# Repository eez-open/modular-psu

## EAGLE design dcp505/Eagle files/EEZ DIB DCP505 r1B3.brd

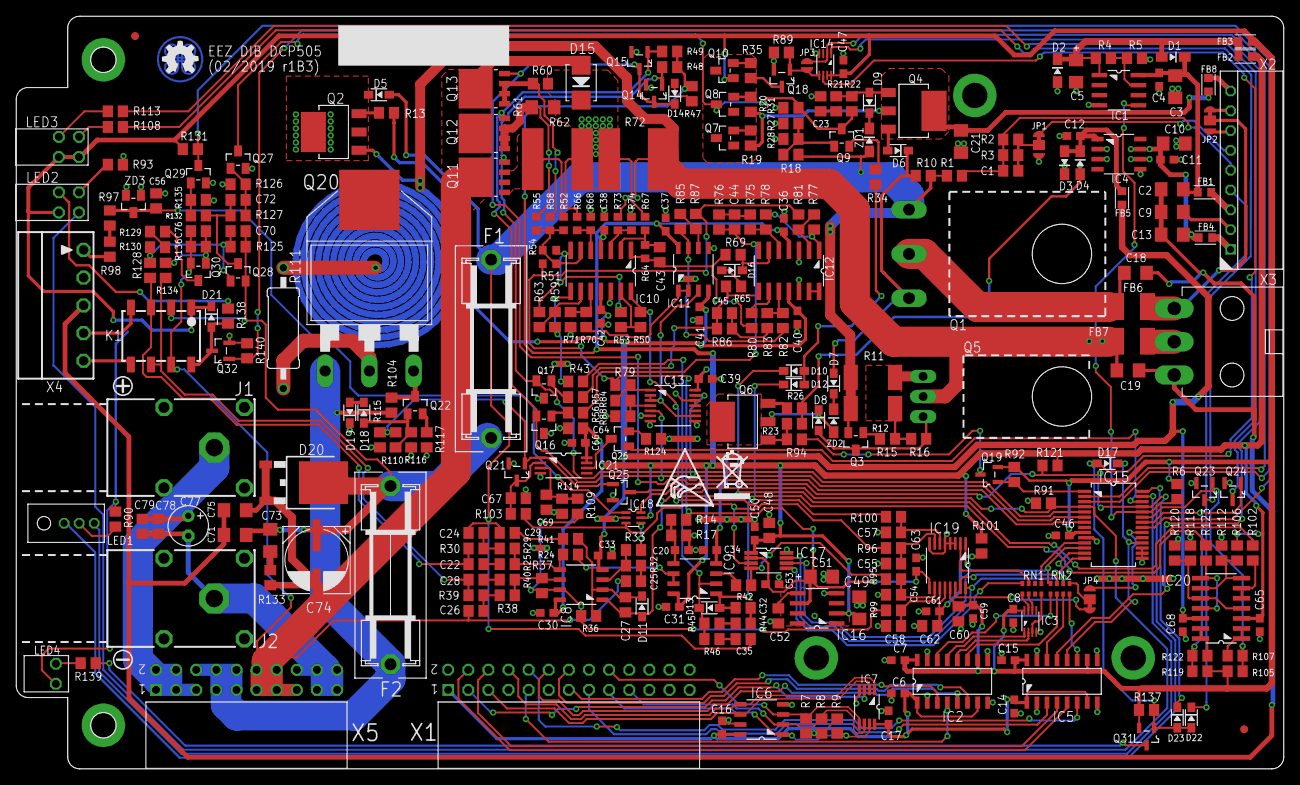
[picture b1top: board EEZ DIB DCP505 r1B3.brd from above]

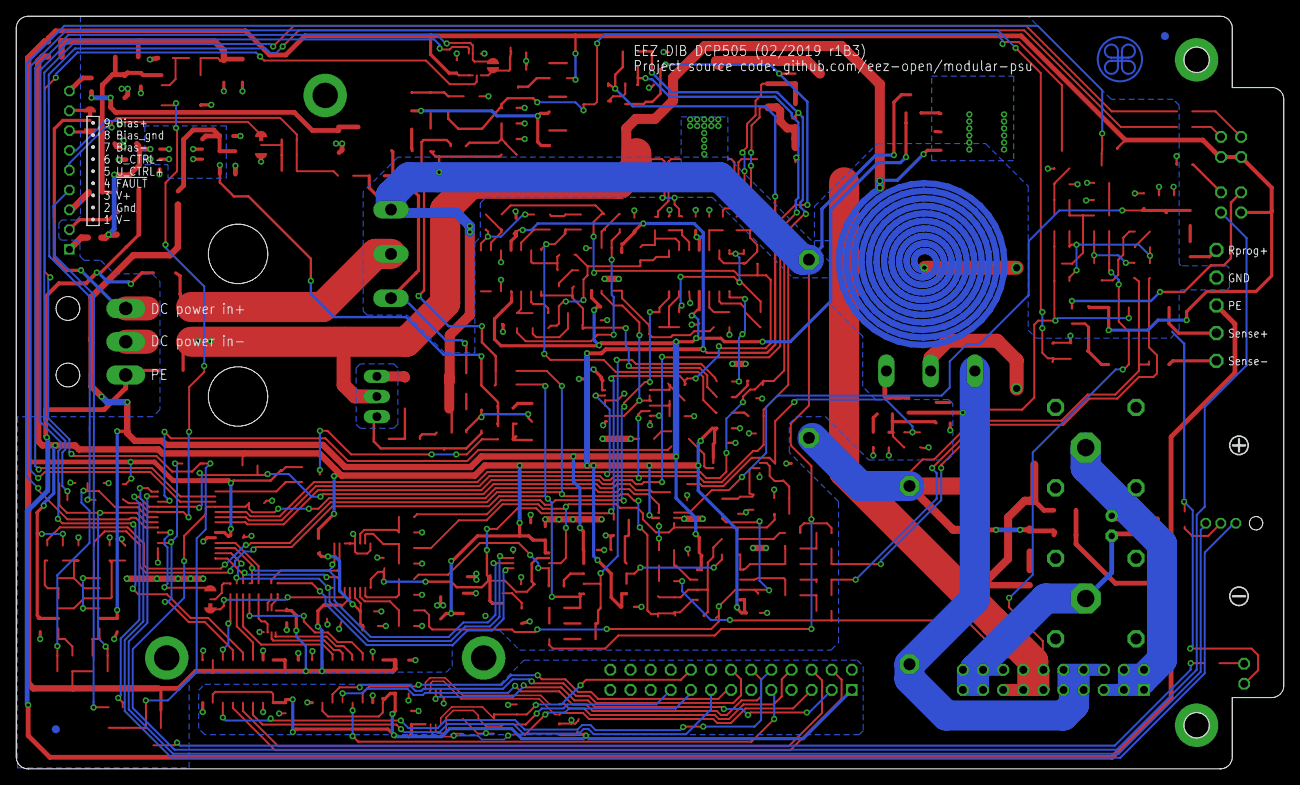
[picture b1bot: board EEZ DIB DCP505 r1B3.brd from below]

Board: 2 copper layers, 160.0 x 95.0 mm, 335 parts (4 on the bottom side), 221 nets.

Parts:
C1, C43: 47n; C0805
C2, C9, C13, C18, C19: 47n; C1206
C3, C10, C49: 10u; C1206
C4, C6, C7, C8, C11, C12, C14, C15, C16, C17, C20, C30, C31, C33, C34, C36, C37, C38, C39, C40, C41, C42, C46, C47, C50, C53, C59, C61, C63, C65, C66, C68: 100n; C0603
C5, C51: 4u7; EC1206
C21: 1u/100V; C1206
C22, C28: 47p; C0805
C23, C44, C45, C56, C70, C76: 10n; C0805
C24, C25, C26, C29, C72: 2n2; C0805
C27: 220p; C0805
C32, C35, C67, C69: 1n; C0805
C48, C52, C60, C62, C64: 1u; C0805
C54, C55, C57, C58: 3n3; C0805
C71, C75: 10n/200V; C1206
C73: 470n; C1206
C74: HHXC630ARA330MHA0G; CAPAE830X1050N
C77: N.C.; ECAP2/5
C78, C79: N.C.; C0805
D1, D2, D3, D4: 1N5819HW-7-F; SOD323-W
D5, D6, D7, D8, D9, D10, D11, D12, D13, D14, D16, D17, D18, D19, D21, D22, D23: BAS316; SOD323-R
D15: SK55; SMB
D20: SK10100D1-DIO; TO252-L
EEZ_SIGNATURE: SIGNATURESMALL; SIGNATURE_5MM
F1, F2: ZH32
FB1, FB2, FB3, FB4, FB5, FB8: BLM18AG102SH1D; BEAD0603
FB6, FB7: BLM41PG600SN1L; L1812
FM1, FM2: FIDUCIAL_2; FIDUCIAL_DUAL
IC1: LP2951; SOIC127P600X175-8N
IC2, IC5: SI8641BB-B-IS1; SOIC-16
IC3: SN74LVC1G139DCUR; DCU8
IC4: MC79L05; SOIC127P600X173-8N
IC6: AT24C04D-SSHM-T; SOIC127P600X173-8N
IC7: TMP1075AIDGK; DGK8
IC8, IC11: MC33272ADR2G; SOIC127P600X173-8N
IC9: MC33274ADR2G; SOIC127P600X173-8N
IC10: OPA4197IDR; SOIC127P600X175-14N
IC12: MC33274ADR2G; SOIC127P600X175-14N
IC13: 74HC4066PW; SOP65P640X120-14N
IC14: 74AUP1G74DC.125; DCU8
IC15: MCP23S17-E/SS; SOP65P780X200-28N
IC16: REF5025AIDR; SOIC127P600X175-8N
IC17: DAC8552IDGKR; DGK8-M
IC18: SN74LVC1G3157DCKR; SOT65P210X110-6N
IC19: ADS1120IPWR; PW(R-PDSO-G16)
IC20: LM339D; SOIC127P600X175-14N
IC21: LM211PWR; PW8_TSSOP8
J1: FCR7350R; S16N-PC
J2: FCR7350B; S16N-PC
JP1, JP2, JP4: JP3-CUT
JP3: JP2-CUT
K1: G6K-2F-5DC; G6K-2F
KK1, KK2: PCB-MB
LED1: L-42WUM/1EGWT; L-42WUM-1EGWT
LED2: L-934EB/2ID; L-934EB
LED3: L-934EB/1Y1ID-RV; L-934EB
LED4: OSY5LU3E34X-3F1A; OSG8
Q1: IRFP250MPBF; TO247BH-CLR2
Q2, Q4, Q6: BCP56-16.115; SOT230P700X180-4N
Q3: BC856C; SOT23-BEC
Q5: STF10P6F6; TO220H-CLR2
Q7, Q8, Q16, Q17, Q28: MMBT5401; SOT23-BEC
Q9, Q10, Q26, Q27, Q29, Q30: MMBT5551; SOT23-BEC
Q11, Q12, Q13: PSMN0R9-25YLC; SOT669
Q14, Q15, Q18, Q21, Q23, Q24, Q25, Q32: 2N7002; SOT103P240X110-3N
Q19, Q31: BSS84P; SOT95P237X112-3N
Q20: BTA26-600; TOP3_TRIAC_NOHOLE
Q22: FMMT493TA; SOT23-BEC
R1, R89, R92, R116, R140: 100K; R0805
R2, R107, R122: 5K6; R0805
R3: 82K; R0805
R4, R18: 16K; R0805
R5, R105, R119: 5K1; R0805
R6, R7, R8, R9, R14, R25, R33, R36, R40, R43, R45, R46, R53, R59, R63, R69, R70, R71, R75, R80, R81, R83, R85, R87, R94, R102, R103, R114, R115, R118, R120, R123, R131, R132, R137: 10K; R0805
R10, R23, R44, R47, R48, R49, R65, R77, R79, R84, R88, R110, R124, R129: 1K; R0805
R11, R12: 3R9/2W; R2512
R13, R28, R109, R128, R134: 750R; R0805
R15, R16, R27, R42, R56, R57, R112, R130: 2K2; R0805
R17, R19, R20, R26, R32, R41, R95, R96, R99, R100: 220R; R0805
R21, R34, R93, R97, R98, R104, R138, R139: 470R; R0805
R22, R78, R82: 100R; R0805
R24, R37: 7K5 0.1%; R0805
R29, R38: 130K 0.1%; R0805
R30, R39: 24K 0.1%; R0805
R31: 51K; R0805
R35: 1K8; R0805
R50: 30K; R0805
R51: 7M5; R0603
R52, R55, R58: 3K 0.1%; R0603
R54, R68: 40K2 0.1%; R0603
R60, R133: 1R; R0805
R61: 0R1; R1206
R62, R72: 0R010; R_H2728
R64, R74: 499K 0.1%; R0603
R66, R67, R73: 1K 0.1%; R0603
R76, R86: 1M; R0805
R90: 270R; R0805
R91, R106, R126, R127, R135: 47K; R0805
R101: 10R; R0805
R108, R113, R125, R136: 330R; R0805
R111: AC01000001007JA100; 0411/15
R117: 6R2; R0805
R121: 4K7; R0805
RN1, RN2: DR1206-33R-4/8; CAY16
SH1, SH2: SHORT_NOHOLE
U$1: RECYCLE_BIN1/8
U$6: ESD_SYMBOL
X1: ZL263-26DG; SSW-113-02-T-D-RA
X2: 22-05-7085; SPOX_22-05-7095
X3: 39-30-3035; MINIFIT_6659-3
X4: 1844249; MC1,5/5-G-3,5
X5: ZL263-20DG; SSW-110-02-T-D-RA
ZD1: BZX384-C15; SOD323-W
ZD2: PDZ6.2B; SOD323-W
ZD3: SLVU2.8-TP; SOT23

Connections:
!DP_DRIVE: Q6.1, R23.1, R94.1
!DRDY: IC19.14, JP4.NC
!FAULT: D22.C, X2.4
!FAULT_OUT: D17.A, D22.A, D23.A, IC14.6, Q31.1, R137.2
!OVP_EN: IC15.26, Q26.B
!OVP_FAULT: D23.C, IC15.25, Q25.3, R121.2
!RESET: D17.C, IC5.12, IC15.18
!SET_DP: IC15.1, Q19.1, R92.2
+3V3: C6.1, C14.1, C16.2, C17.1, IC2.1, IC2.7, IC5.1, IC5.7, IC6.8, IC7.8, R7.1, R8.1, R9.1, X1.1
+5V: C7.2, C8.1, C15.2, C46.1, C47.2, C59.2, C60.2, D21.C, FB3.P$2, IC2.10, IC2.16, IC3.8, IC5.10, IC5.16, IC14.7, IC14.8, IC15.9, IC19.13, K1.1, LED2.BA, LED3.BA, LED3.TA, Q10.B, Q19.2, Q31.2, R6.1, R92.1, R105.2, R119.2, R131.2, R137.1
+5VOUT: C5.+, D1.A, D2.C, FB2.P$1, FB3.P$1, IC1.1, R4.1
+6V: C2.1, C3.1, C4.1, D1.C, FB1.P$2, IC1.8
+VREF: C51.+, C53.2, C63.2, IC16.6, IC17.2, IC19.9, R14.1, R51.1, R79.2, R81.2, R87.2
-5VOUT: C12.2, D3.A, D4.C, FB5.P$1, IC4.1
-9V: C10.2, C11.2, C13.1, D4.A, FB4.P$2, IC4.2, IC4.3, IC4.6, IC4.7, R23.2, R26.2
AUX_IN: C56.2, IC18.1, R97.1, ZD3.3
AUX_USET_SW: IC15.4, IC18.6, LED2.TA, R91.2
BIAS_IN+: FB8.P$1, X2.9
CCS_HS: D5.C, Q2.2, Q2.4
CC_ACTIVE: IC15.22, Q24.1, R119.1, R122.2
CC_LED: LED3.BC, R113.2
CSA: IC2.13, IC3.1
CSB: IC2.12, IC3.2
CS_ADC: IC19.2, RN1.7
CS_DAC: IC17.5, RN1.8
CS_IOEXP: IC15.11, RN1.5
CURR_5A: IC13.13, IC15.5, Q11.4, Q14.1, Q17.E, R48.2
CURR_50MA: D14.C, IC13.6, IC15.7, Q13.4, Q14.3, Q15.3
CURR_500MA: IC13.5, IC15.6, Q12.4, Q15.1, Q16.E, R49.2
CV_ACTIVE: IC15.23, Q23.1, R105.1, R107.2
CV_LED: LED3.TC, R108.1
DC_BIAS: C21.1, FB8.P$2, Q4.2, Q4.4, R19.2, R20.2
DIB_5V: X1.23, X1.24
DIB_12V: X1.21, X1.22
DIB_A0: IC6.1, IC7.7, R9.2, X1.17
DIB_A1: IC6.2, IC7.6, R8.2, X1.19
DIB_A2: IC6.3, IC7.5, R7.2, X1.18
DIB_CSA: IC2.4, X1.9
DIB_CSB: IC2.5, X1.12
DIB_IRQ: IC5.6, X1.10
DIB_MISO: IC2.6, X1.14
DIB_MOSI: IC5.3, X1.15
DIB_NFAULT: IC7.3, X1.3
DIB_NRESET: IC5.5, X1.4
DIB_SCL: IC6.6, IC7.2, X1.5
DIB_SCLK: IC2.3, X1.13
DIB_SDA: IC6.5, IC7.1, X1.8
DP_LED: Q19.3, R94.2
DP_S: Q5.3, R11.1, R12.1, R15.1, R16.1
GCOM: IC9.6, IC9.7, R24.1
GND: C3.2, C4.2, C5.-, C7.1, C8.2, C9.1, C10.1, C11.1, C12.1, C15.1, C20.2, C21.2, C23.2, C30.1, C31.1, C33.1, C34.1, C36.2, C37.2, C38.2, C39.1, C40.2, C41.2, C42.2, C46.2, C47.1, C48.2, C49.2, C50.1, C51.-, C52.2, C53.1, C54.1, C55.1, C56.1, C57.2, C58.1, C59.1, C60.1, C61.1, C62.1, C63.1, C64.2, C65.1, C66.1, C67.1, C68.1, C69.1, D2.A, D3.C, D19.C, IC1.4, IC2.9, IC2.15, IC3.4, IC4.5, IC5.9, IC5.15, IC10.12, IC11.5, IC12.3, IC12.12, IC13.7, IC13.8, IC13.11, IC13.12, IC14.4, IC15.10, IC15.15, IC15.16, IC15.17, IC16.4, IC17.8, IC18.2, IC19.3, IC19.4, IC19.5, IC19.8, IC21.4, JP1.NO, LED4.C, Q14.2, Q15.2, Q16.C, Q17.C, Q18.2, Q21.2, Q23.2, Q24.2, Q25.2, Q27.E, Q29.E, Q32.2, R5.2, R17.2, R27.1, R28.1, R31.1, R68.1, R71.1, R74.2, R88.1, R89.1, R90.2, R91.1, R93.1, R112.1, R114.2, R115.2, R116.1, R117.1, R118.2, R124.2, R126.1, R135.1, R140.1, SH2.P$2, X2.2, X4.2, ZD3.1, ZD3.2
GNDIO: C6.2, C14.2, C16.1, C17.2, IC2.2, IC2.8, IC5.2, IC5.8, IC6.4, IC6.7, IC7.4, X1.7, X1.11, X1.16, X1.20, X1.25, X1.26
IRQ: JP4.COM, RN2.5
ISENSE+: IC10.6, R51.2, R52.2, R54.1, R55.2, R58.2
ISENSE-: IC10.5, R66.2, R68.2
I_CTRL: IC10.8, R43.1, R59.2
I_MON: IC10.14, R50.2, R100.1
I_SERVO: C32.2, D12.C, D13.A, IC9.1, R123.1
I_SET: IC17.4, R42.1, R95.1
LOOP_CTRL: D10.A, D12.A, R34.1
MISO: IC15.14, IC19.15, RN2.7
MOSI: IC15.13, IC17.7, IC19.16, RN2.6
unnamed: R67.2, R72.2S
unnamed: FB1.P$1, X2.3
unnamed: IC15.20, JP4.NO
unnamed: C70.1, C71.1, C73.1, C74.+, D20.3, F1.2, F2.1, K1.2, Q28.E, R125.2
unnamed: FB4.P$1, X2.1
unnamed: IC3.7, RN1.1
unnamed: D15.C, R60.2, R61.1, R62.1, R72.2
unnamed: IC11.1, IC11.2, R70.2
unnamed: IC2.11, RN2.2
unnamed: IC5.11, RN2.4
unnamed: FB7.1, X3.2
unnamed: LED1.CC, R90.1
unnamed: C1.2, JP1.COM, R2.2, R3.2
unnamed: Q20.A2, R111.2
unnamed: LED4.A, R139.1
unnamed: R97.2, R98.1
unnamed: Q20.G, Q22.C, R104.1
unnamed: Q22.E, R117.2
unnamed: D18.C, D19.A
unnamed: D18.A, Q22.B, R110.1, R116.2
unnamed: IC3.6, RN1.2
unnamed: IC11.6, R85.2, R87.1
unnamed: IC21.6, Q26.C
unnamed: Q31.3, R139.2
unnamed: IC3.3, RN1.4
unnamed: C43.1, IC10.2, R64.2, R67.1
unnamed: Q11.1, Q11.2, Q11.3, R62.2
unnamed: Q26.E, R124.1
unnamed: C67.2, IC21.2, Q21.3, R103.2
unnamed: R98.2, X4.1
unnamed: C69.2, IC21.3, R109.2, R114.1
unnamed: D14.A, R47.2
unnamed: C43.2, IC10.1, R64.1, R69.2, R80.2
unnamed: IC11.3, IC13.2, IC13.3, IC13.9
unnamed: C44.2, IC12.7, R56.2, R76.1
unnamed: Q16.B, R56.1
unnamed: Q17.B, R57.1
unnamed: IC10.7, R53.1, R54.2, R63.1
unnamed: IC10.9, R59.1, R63.2
unnamed: IC13.1, R79.1, R84.2
unnamed: C45.2, IC12.8, R57.2, R65.2, R86.1
unnamed: IC10.10, R70.1, R71.2
unnamed: IC14.5, JP3.2, Q18.1, R89.2
unnamed: Q24.3, R113.1
unnamed: IC13.4, R84.1, R88.2
unnamed: IC11.7, R82.2, R85.1
unnamed: IC10.13, R50.1, R53.2
unnamed: R72.1S, R73.2
unnamed: R62.1S, R66.1
unnamed: IC12.2, R77.2, R81.1
unnamed: IC12.1, R77.1, R78.2
unnamed: IC10.3, R73.1, R74.1
unnamed: IC12.13, IC12.14
unnamed: Q12.1, Q12.2, Q12.3, R55.1, R61.2
unnamed: D16.C, IC12.6, R69.1
unnamed: IC12.5, R75.2, R78.1
unnamed: R52.1, R62.2S
unnamed: IC12.9, R80.1
unnamed: IC5.14, RN2.3
unnamed: IC12.10, R82.1, R83.2
unnamed: Q13.1, Q13.2, Q13.3, R58.1, R60.1
unnamed: JP2.NO, X2.7
unnamed: C44.1, R75.1, R76.2
unnamed: JP2.NC, X2.8
unnamed: C45.1, R83.1, R86.2
unnamed: C61.2, C62.2, IC19.12, R101.2
unnamed: C52.1, IC16.5
unnamed: C54.2, IC19.10, R95.2
unnamed: C58.2, IC19.11, R99.2
unnamed: D16.A, R65.1
unnamed: C55.2, IC19.7, R96.2
unnamed: C57.1, IC19.6, R100.2
unnamed: IC9.3, R42.2
unnamed: IC8.3, R32.2, R33.2
unnamed: C27.1, D11.C, IC8.2, R36.2, R41.2
unnamed: C26.1, R38.2, R39.1
unnamed: C22.2, R25.1
unnamed: C28.2, R40.1
unnamed: C35.2, R46.1
unnamed: D13.C, IC9.2, R43.2, R45.2, R46.2
unnamed: C25.2, R32.1
unnamed: C29.2, R41.1
unnamed: D6.C, D7.A, Q1.1, R10.1
unnamed: D6.A, Q4.3
unnamed: D9.A, Q4.1, R21.2, R22.1
unnamed: C23.1, R21.1
unnamed: Q9.B, R18.1, R27.2, R28.2
unnamed: Q6.3, R26.1
unnamed: Q3.B, R15.2
unnamed: IC1.7, R4.2, R5.1
unnamed: C20.1, IC9.5, R14.2, R17.1
unnamed: IC20.1, IC20.2, R107.1
unnamed: IC20.13, IC20.14, R122.1
unnamed: C70.2, Q28.B, R125.1, R128.2, R130.2
unnamed: C72.2, Q28.C, R127.1, R132.2
unnamed: Q30.C, R129.1
unnamed: C76.1, Q30.B, R134.1, R136.2
unnamed: C72.1, Q27.B, R126.2, R127.2
unnamed: Q29.B, R132.1, R135.2
unnamed: C73.2, R133.2
unnamed: D21.A, K1.8, Q32.3, R138.1
unnamed: K1.4, X4.4
unnamed: K1.5, X4.5
unnamed: C24.1, R29.2, R30.1
unnamed: Q23.3, R108.2
unnamed: LED2.BC, R138.2
unnamed: LED2.TC, R93.2
unnamed: IC2.14, RN2.1
unnamed: D9.C, ZD1.C
unnamed: D7.C, ZD2.C
unnamed: Q9.E, R34.2
unnamed: D8.A, Q3.C, Q5.1, R16.2
unnamed: IC8.5, R24.2, R25.2, R29.1
unnamed: IC20.5, IC20.6, R102.2
unnamed: IC8.6, R37.2, R38.1, R40.2
unnamed: R44.2, R45.1
unnamed: IC20.8, IC20.11, R123.2
unnamed: C32.1, R44.1
unnamed: Q2.3, R13.2
unnamed: IC20.7, IC20.9, R106.1, R112.2
unnamed: R129.2, R130.1
unnamed: IC20.4, IC20.10, R118.1, R120.2
unnamed: Q8.E, R20.1
unnamed: Q7.E, R19.1
unnamed: Q10.E, R35.2
OE_GREEN: IC15.27, LED1.GREEN
OE_RED: IC15.28, LED1.RED
OE_SYNC: IC5.4, X1.6
OE_TRIG: IC5.13, IC14.1
OUTC+: C77.+, C78.1, C79.1, J1.1, J1.NC1, J1.NC2, J1.NC3, J1.NC4, X5.1, X5.2, X5.3, X5.4, X5.5
OUTC-: C77.-, C78.2, C79.2, J2.1, J2.NC1, J2.NC2, J2.NC3, J2.NC4, X5.16, X5.17, X5.18, X5.19, X5.20
OUTF+: F2.2, Q20.A1, R104.2, X5.6, X5.7, X5.8, X5.9, X5.10
OVP_FAULT: IC21.1, Q21.1, Q25.1, R110.2, R115.1
PE: C2.2, C9.2, C13.2, C18.2, C19.2, C71.2, C75.1, X3.3, X4.3
POST_OE: Q18.3, R35.1
POST_OUT+: C24.2, C29.1, C35.1, D5.A, F1.1, Q1.3, Q3.E, R1.1, R10.2, R11.2, R12.2, R18.2, ZD1.A
POST_OUT-: C25.1, C26.2, C74.-, C75.2, C76.2, D15.A, D20.1, D20.2, K1.7, Q11.MB, Q12.MB, Q13.MB, Q30.E, R133.1, R136.1, X5.11, X5.12, X5.13, X5.14, X5.15
PREG_IN+: FB6.1, JP2.COM, X3.1
PREG_IN-: C19.1, FB7.2, Q5.2, SH1.P$1, SH2.P$1
PREG_OUT+: C18.1, FB6.2, Q1.2
PREG_OUT-: Q2.1, R72.1, R111.1, SH1.P$2
PRE_OE: IC14.2, IC15.2, JP3.1
PWRGOOD: IC1.5, IC15.24, R6.2
Q6C: D8.C, Q6.2, Q6.4, ZD2.A
Q7C: Q7.B, Q7.C, Q8.B, Q10.C
RSENSE: IC15.3, Q32.1, R140.2
SCLK: IC15.12, IC17.6, IC19.1, RN2.8
SENSE+: C22.1, K1.3, R30.2, R128.1
SENSE-: C28.1, K1.6, R39.2, R134.2
SENSE_ERR: IC15.21, Q29.C, R131.1
SENSE_PROT: Q8.C, Q9.C, Q27.C, R22.2, R31.2
U_CTRL+: C1.1, R1.2, R2.1, R3.1, X2.5
U_CTRL-: JP1.NC, X2.6
U_MON: IC8.7, R36.1, R37.1, R99.1, R109.1
U_SERVO: C27.2, D10.C, D11.A, IC8.1, R102.1
U_SET: IC17.3, IC18.3, R96.1, R103.1
U_SET_OUT: IC18.4, R33.1
V+: C30.2, C31.2, C36.1, C37.1, C38.1, C39.2, C48.1, C49.1, C50.2, C64.1, C65.2, C66.2, FB2.P$2, IC8.8, IC9.8, IC10.4, IC11.8, IC12.4, IC13.14, IC16.2, IC17.1, IC18.5, IC20.3, IC21.7, IC21.8, R47.1, R48.1, R49.1, R101.1, R106.2, R121.1
V-: C33.2, C34.2, C40.1, C41.1, C42.1, C68.2, FB5.P$2, IC8.4, IC9.4, IC10.11, IC11.4, IC12.11, IC20.12, R13.1, R120.1

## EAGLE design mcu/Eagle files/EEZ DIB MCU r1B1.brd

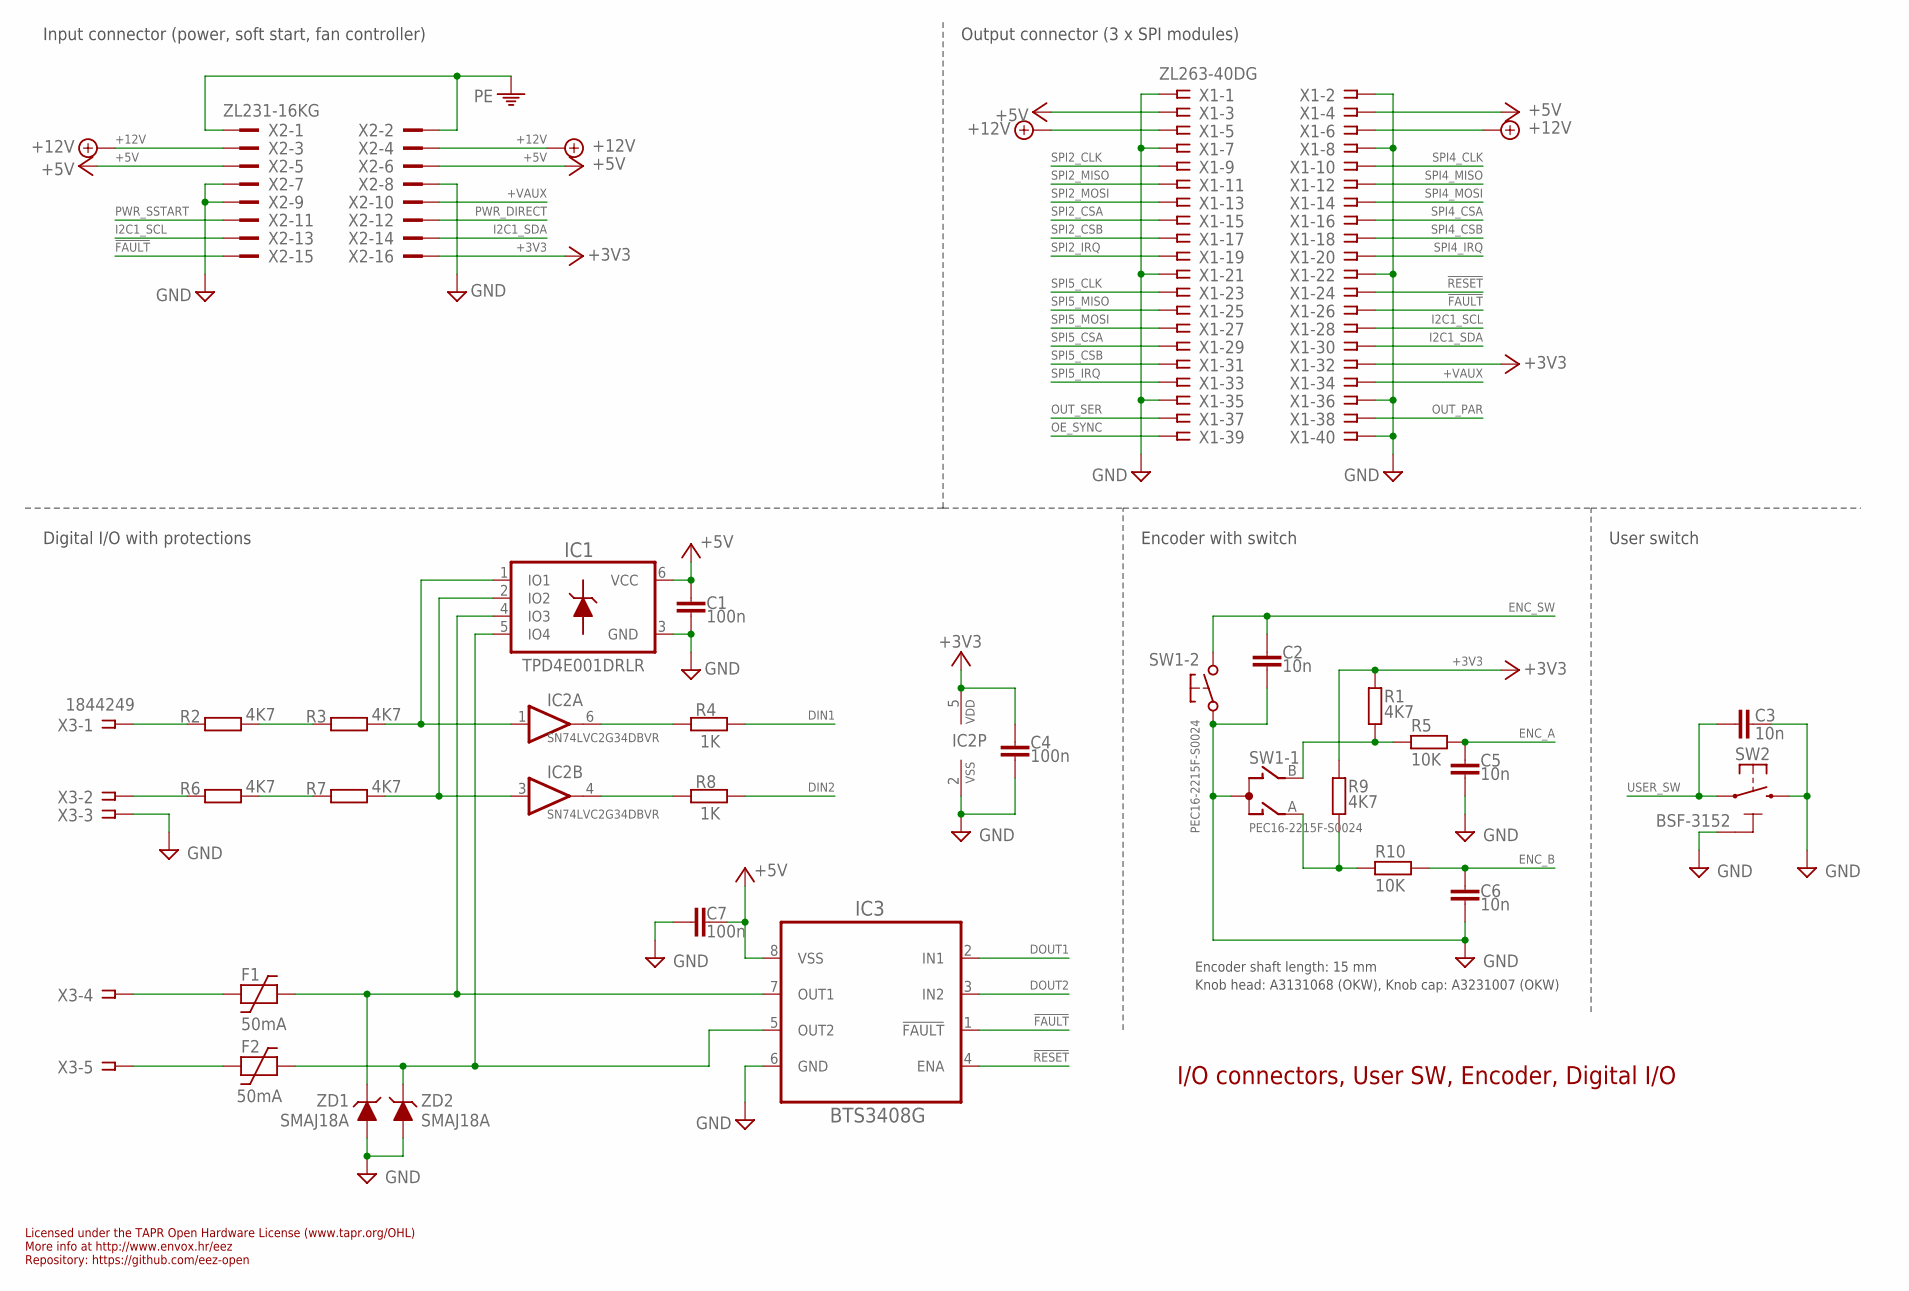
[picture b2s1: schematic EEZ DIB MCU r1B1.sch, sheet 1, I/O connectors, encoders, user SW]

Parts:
C1, C4, C7: 100n; C0603
C2, C3, C5, C6: 10n; C0805
F1, F2: 50mA; F1210
IC1: TPD4E001DRLR; DRL6
IC2: SN74LVC2G34DBVR; DBV6
IC3: BTS3408G; SOIC127P600X173-8N
R1, R2, R3, R6, R7, R9: 4K7; R0805
R4, R8: 1K; R0805
R5, R10: 10K; R0805
SW1: PEC16-2215F-S0024; PEC16-2215F
SW2: BSF-3152; BSF-315X
X1: ZL263-40DG
X2: ZL231-16KG; ML16L
X3: 1844249; MC1,5/5-G-3,5
ZD1, ZD2: SMAJ18A; DO214AC

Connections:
!FAULT: IC3.1 (!FAULT), X1.26, X2.15; also elsewhere on the board
!RESET: IC3.4 (ENA), X1.24; also elsewhere on the board
+3V3: C4.1, IC2.5 (VDD), R1.1, R9.1, X1.32, X2.16; also elsewhere on the board
+5V: C1.1, C7.2, IC1.6 (VCC), IC3.8 (VSS), X1.3, X1.4, X2.5, X2.6; also elsewhere on the board
+12V: X1.5, X1.6, X2.3, X2.4
+VAUX: X1.34, X2.10
DIN1: R4.2; also elsewhere on the board
DIN2: R8.2; also elsewhere on the board
DOUT1: IC3.2 (IN1); also elsewhere on the board
DOUT2: IC3.3 (IN2); also elsewhere on the board
ENC_A: C5.2, R5.1; also elsewhere on the board
ENC_B: C6.1, R10.1; also elsewhere on the board
ENC_SW: C2.2, SW1.E (2); also elsewhere on the board
EOUT_A: R9.2, R10.2, SW1.A
EOUT_B: R1.2, R5.2, SW1.B
GND: C1.2, C2.1, C3.1, C4.2, C5.1, C6.2, C7.1, IC1.3 (GND), IC2.2 (VSS), IC3.6 (GND), SW1.C, SW1.D (1), SW1.GND1 (C), SW1.GND2 (C), SW2.2, SW2.3 (GND), SW2.4 (GND), X1.1, X1.2, X1.7, X1.8, X1.21, X1.22, X1.35, X1.36, X1.40, X2.7, X2.8, X2.9, X3.3, ZD1.A, ZD2.A; also elsewhere on the board
I2C1_SCL: X1.28, X2.13; also elsewhere on the board
I2C1_SDA: X1.30, X2.14; also elsewhere on the board
unnamed: R2.2, R3.1
unnamed: R2.1, X3.1
unnamed: R6.1, X3.2
unnamed: R6.2, R7.1
unnamed: IC2.6 (O), R4.1
unnamed: IC2.4 (O), R8.1
unnamed: F1.1, X3.4
unnamed: F2.1, X3.5
unnamed: IC1.1 (IO1), IC2.1 (I), R3.2
unnamed: IC1.2 (IO2), IC2.3 (I), R7.2
unnamed: F1.2, IC1.4 (IO3), IC3.7 (OUT1), ZD1.C
unnamed: F2.2, IC1.5 (IO4), IC3.5 (OUT2), ZD2.C
OE_SYNC: X1.39; also elsewhere on the board
OUT_PAR: X1.38; also elsewhere on the board
OUT_SER: X1.37; also elsewhere on the board
PE: X2.1, X2.2; also elsewhere on the board
PWR_DIRECT: X2.12; also elsewhere on the board
PWR_SSTART: X2.11; also elsewhere on the board
SPI2_CLK: X1.9; also elsewhere on the board
SPI2_CSA: X1.15; also elsewhere on the board
SPI2_CSB: X1.17; also elsewhere on the board
SPI2_IRQ: X1.19; also elsewhere on the board
SPI2_MISO: X1.11; also elsewhere on the board
SPI2_MOSI: X1.13; also elsewhere on the board
SPI4_CLK: X1.10; also elsewhere on the board
SPI4_CSA: X1.16; also elsewhere on the board
SPI4_CSB: X1.18; also elsewhere on the board
SPI4_IRQ: X1.20; also elsewhere on the board
SPI4_MISO: X1.12; also elsewhere on the board
SPI4_MOSI: X1.14; also elsewhere on the board
SPI5_CLK: X1.23; also elsewhere on the board
SPI5_CSA: X1.29; also elsewhere on the board
SPI5_CSB: X1.31; also elsewhere on the board
SPI5_IRQ: X1.33; also elsewhere on the board
SPI5_MISO: X1.25; also elsewhere on the board
SPI5_MOSI: X1.27; also elsewhere on the board
USER_SW: C3.2, SW2.1; also elsewhere on the board

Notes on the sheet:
Licensed under the TAPR Open Hardware License (www.tapr.org/OHL)
Repository: https://github.com/eez-open
More info at http://www.envox.hr/eez
Encoder shaft length: 15 mm
Knob head: A3131068 (OKW), Knob cap: A3231007 (OKW)
I/O connectors, User SW, Encoder, Digital I/O
Digital I/O with protections
Encoder with switch
User switch
Input connector (power, soft start, fan controller)
Output connector (3 x SPI modules)

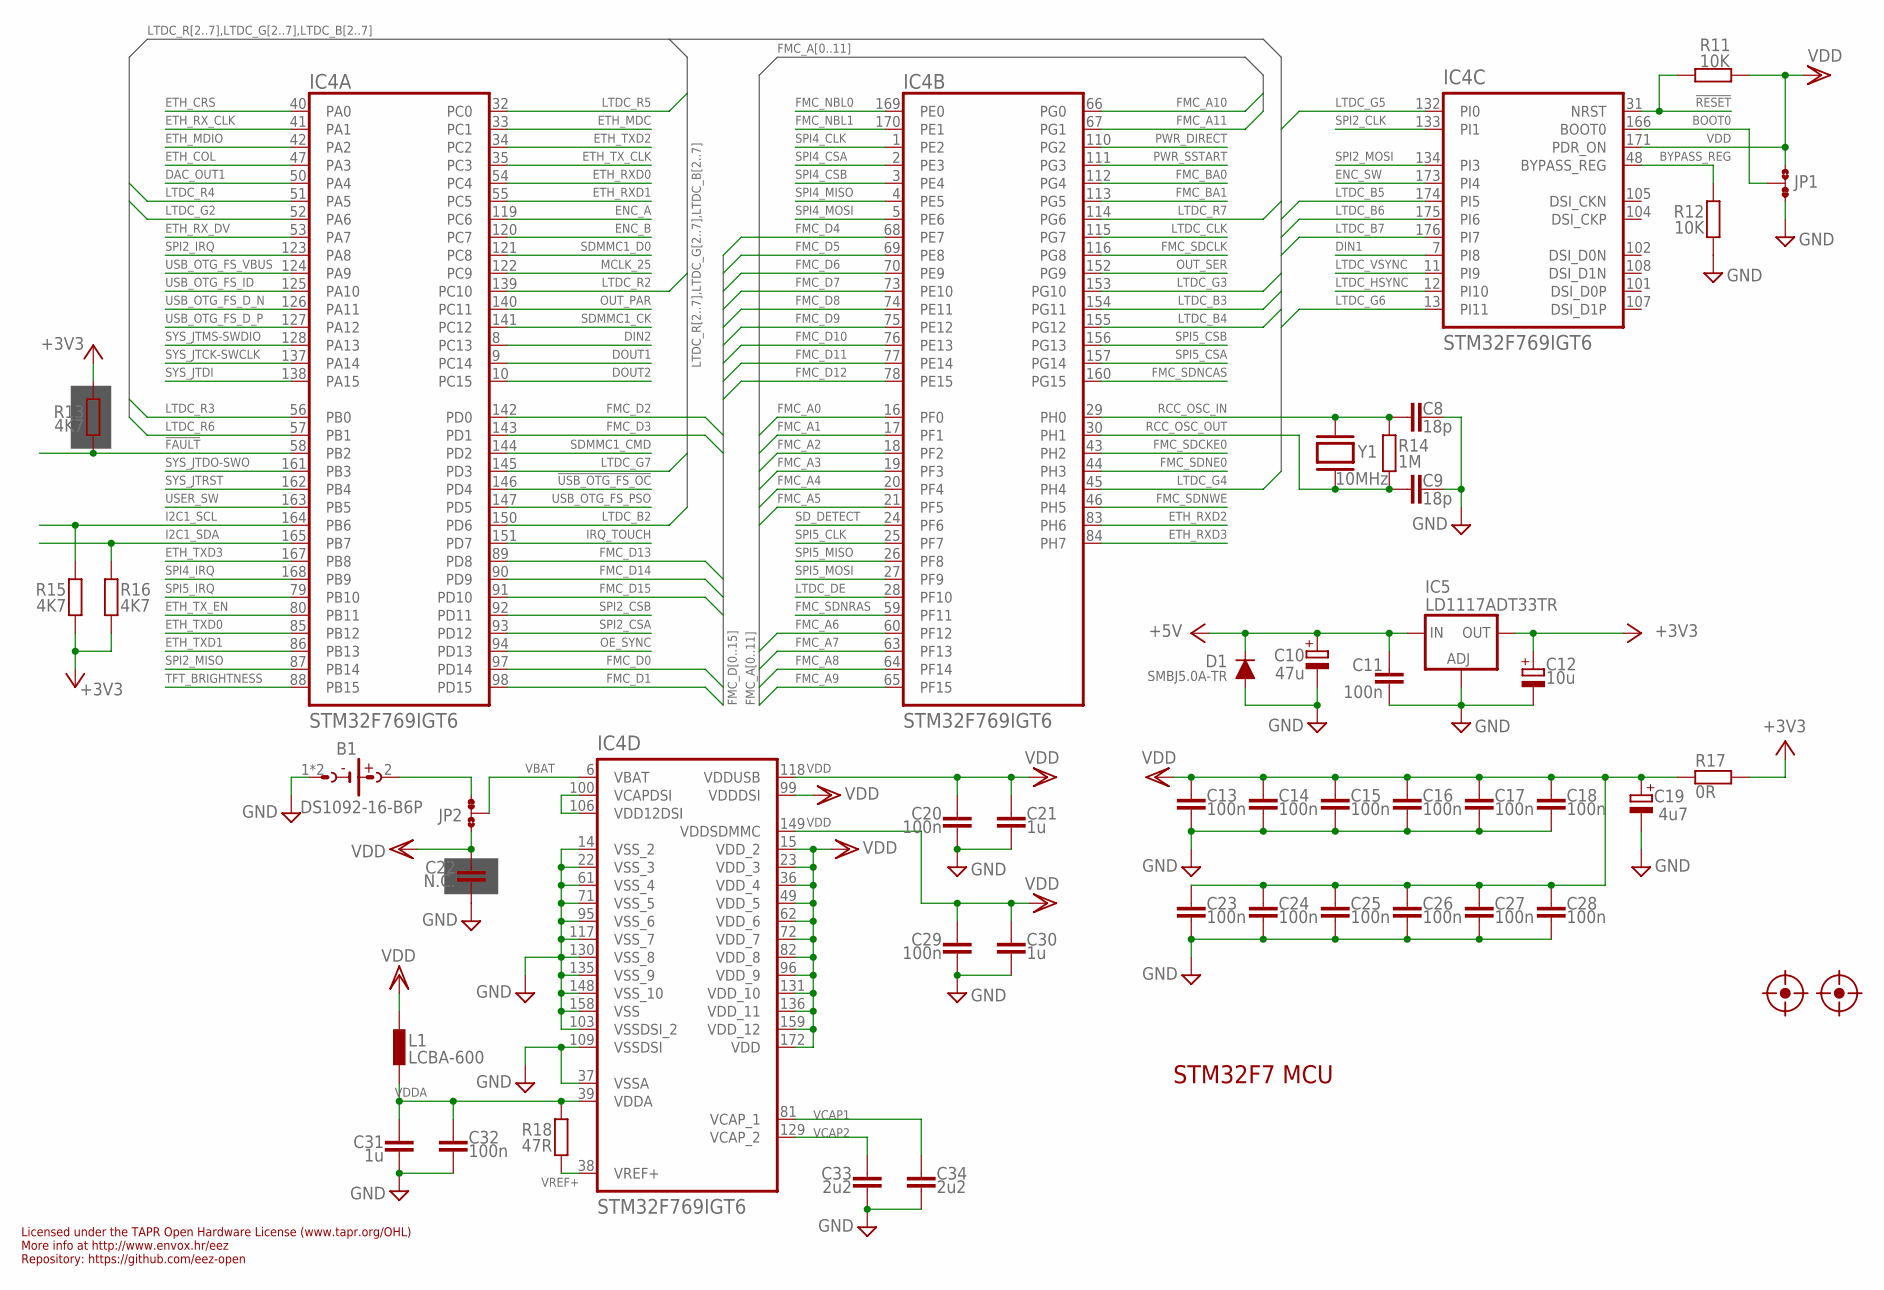
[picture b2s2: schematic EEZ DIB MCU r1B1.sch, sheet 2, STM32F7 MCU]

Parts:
B1: DS1092-16-B6P
C8, C9: 18p; C0603
C10: 47u; CAPAE660X610N
C11, C13, C14, C15, C16, C17, C18, C20, C23, C24, C25, C26, C27, C28, C29, C32: 100n; C0603
C12: 10u; EC1206
C19: 4u7; EC1206
C21, C30, C31: 1u; C0805
C22: N.C.; C0603
C33, C34: 2u2; C0805
D1: SMBJ5.0A-TR; DO214AA
FM1, FM2: FIDUCIAL
IC4: STM32F769IGT6; LQFP-176_24X24MM
IC5: LD1117ADT33TR; DPACK
JP1, JP2: JP3-CUT
L1: LCBA-600; BEAD0603
R11, R12: 10K; R0805
R13, R15, R16: 4K7; R0805
R14: 1M; R0805
R17: 0R; R0805
R18: 47R; R0805
Y1: 10MHz; HC-49/4H

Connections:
!FAULT: IC4.58 (PB2), R13.2; also elsewhere on the board
!RESET: IC4.31 (NRST), R11.2; also elsewhere on the board
!USB_OTG_FS_OC: IC4.146 (PD4); also elsewhere on the board
+3V3: C12.+, IC5.4 (OUT), R13.1, R15.1, R16.1, R17.1; also elsewhere on the board
+5V: C10.1 (+), C11.1, D1.C, IC5.3 (IN); also elsewhere on the board
BOOT0: IC4.166 (BOOT0), JP1.COM
BYPASS_REG: IC4.48 (BYPASS_REG), R12.2
DAC_OUT1: IC4.50 (PA4); also elsewhere on the board
DIN1: IC4.7 (PI8); also elsewhere on the board
DIN2: IC4.8 (PC13); also elsewhere on the board
DOUT1: IC4.9 (PC14); also elsewhere on the board
DOUT2: IC4.10 (PC15); also elsewhere on the board
ENC_A: IC4.119 (PC6); also elsewhere on the board
ENC_B: IC4.120 (PC7); also elsewhere on the board
ENC_SW: IC4.173 (PI4); also elsewhere on the board
ETH_COL: IC4.47 (PA3); also elsewhere on the board
ETH_CRS: IC4.40 (PA0); also elsewhere on the board
ETH_MDC: IC4.33 (PC1); also elsewhere on the board
ETH_MDIO: IC4.42 (PA2); also elsewhere on the board
ETH_RXD0: IC4.54 (PC4); also elsewhere on the board
ETH_RXD1: IC4.55 (PC5); also elsewhere on the board
ETH_RXD2: IC4.83 (PH6); also elsewhere on the board
ETH_RXD3: IC4.84 (PH7); also elsewhere on the board
ETH_RX_CLK: IC4.41 (PA1); also elsewhere on the board
ETH_RX_DV: IC4.53 (PA7); also elsewhere on the board
ETH_TXD0: IC4.85 (PB12); also elsewhere on the board
ETH_TXD1: IC4.86 (PB13); also elsewhere on the board
ETH_TXD2: IC4.34 (PC2); also elsewhere on the board
ETH_TXD3: IC4.167 (PB8); also elsewhere on the board
ETH_TX_CLK: IC4.35 (PC3); also elsewhere on the board
ETH_TX_EN: IC4.80 (PB11); also elsewhere on the board
FMC_A0: IC4.16 (PF0); also elsewhere on the board
FMC_A1: IC4.17 (PF1); also elsewhere on the board
FMC_A2: IC4.18 (PF2); also elsewhere on the board
FMC_A3: IC4.19 (PF3); also elsewhere on the board
FMC_A4: IC4.20 (PF4); also elsewhere on the board
FMC_A5: IC4.21 (PF5); also elsewhere on the board
FMC_A6: IC4.60 (PF12); also elsewhere on the board
FMC_A7: IC4.63 (PF13); also elsewhere on the board
FMC_A8: IC4.64 (PF14); also elsewhere on the board
FMC_A9: IC4.65 (PF15); also elsewhere on the board
FMC_A10: IC4.66 (PG0); also elsewhere on the board
FMC_A11: IC4.67 (PG1); also elsewhere on the board
FMC_BA0: IC4.112 (PG4); also elsewhere on the board
FMC_BA1: IC4.113 (PG5); also elsewhere on the board
FMC_D0: IC4.97 (PD14); also elsewhere on the board
FMC_D1: IC4.98 (PD15); also elsewhere on the board
FMC_D2: IC4.142 (PD0); also elsewhere on the board
FMC_D3: IC4.143 (PD1); also elsewhere on the board
FMC_D4: IC4.68 (PE7); also elsewhere on the board
FMC_D5: IC4.69 (PE8); also elsewhere on the board
FMC_D6: IC4.70 (PE9); also elsewhere on the board
FMC_D7: IC4.73 (PE10); also elsewhere on the board
FMC_D8: IC4.74 (PE11); also elsewhere on the board
FMC_D9: IC4.75 (PE12); also elsewhere on the board
FMC_D10: IC4.76 (PE13); also elsewhere on the board
FMC_D11: IC4.77 (PE14); also elsewhere on the board
FMC_D12: IC4.78 (PE15); also elsewhere on the board
FMC_D13: IC4.89 (PD8); also elsewhere on the board
FMC_D14: IC4.90 (PD9); also elsewhere on the board
FMC_D15: IC4.91 (PD10); also elsewhere on the board
FMC_NBL0: IC4.169 (PE0); also elsewhere on the board
FMC_NBL1: IC4.170 (PE1); also elsewhere on the board
FMC_SDCKE0: IC4.43 (PH2); also elsewhere on the board
FMC_SDCLK: IC4.116 (PG8); also elsewhere on the board
FMC_SDNCAS: IC4.160 (PG15); also elsewhere on the board
FMC_SDNE0: IC4.44 (PH3); also elsewhere on the board
FMC_SDNRAS: IC4.59 (PF11); also elsewhere on the board
FMC_SDNWE: IC4.46 (PH5); also elsewhere on the board
GND: B1.1 (-), B1.3 (-), C8.1, C9.1, C10.2 (-), C11.2, C12.-, C13.2, C14.2, C15.2, C16.2, C17.2, C18.2, C19.-, C20.2, C21.2, C22.2, C23.2, C24.2, C25.2, C26.2, C27.2, C28.2, C29.2, C30.2, C31.2, C32.2, C33.2, C34.2, D1.A, IC4.14 (VSS_2), IC4.22 (VSS_3), IC4.37 (VSSA), IC4.61 (VSS_4), IC4.71 (VSS_5), IC4.95 (VSS_6), IC4.103 (VSSDSI_2), IC4.109 (VSSDSI), IC4.117 (VSS_7), IC4.130 (VSS_8), IC4.135 (VSS_9), IC4.148 (VSS_10), IC4.158 (VSS), IC5.1 (ADJ), JP1.NC, R12.1; also elsewhere on the board
I2C1_SCL: IC4.164 (PB6), R15.2; also elsewhere on the board
I2C1_SDA: IC4.165 (PB7), R16.2; also elsewhere on the board
IRQ_TOUCH: IC4.151 (PD7); also elsewhere on the board
LTDC_B2: IC4.150 (PD6); also elsewhere on the board
LTDC_B3: IC4.154 (PG11); also elsewhere on the board
LTDC_B4: IC4.155 (PG12); also elsewhere on the board
LTDC_B5: IC4.174 (PI5); also elsewhere on the board
LTDC_B6: IC4.175 (PI6); also elsewhere on the board
LTDC_B7: IC4.176 (PI7); also elsewhere on the board
LTDC_CLK: IC4.115 (PG7); also elsewhere on the board
LTDC_DE: IC4.28 (PF10); also elsewhere on the board
LTDC_G2: IC4.52 (PA6); also elsewhere on the board
LTDC_G3: IC4.153 (PG10); also elsewhere on the board
LTDC_G4: IC4.45 (PH4); also elsewhere on the board
LTDC_G5: IC4.132 (PI0); also elsewhere on the board
LTDC_G6: IC4.13 (PI11); also elsewhere on the board
LTDC_G7: IC4.145 (PD3); also elsewhere on the board
LTDC_HSYNC: IC4.12 (PI10); also elsewhere on the board
LTDC_R2: IC4.139 (PC10); also elsewhere on the board
LTDC_R3: IC4.56 (PB0); also elsewhere on the board
LTDC_R4: IC4.51 (PA5); also elsewhere on the board
LTDC_R5: IC4.32 (PC0); also elsewhere on the board
LTDC_R6: IC4.57 (PB1); also elsewhere on the board
LTDC_R7: IC4.114 (PG6); also elsewhere on the board
LTDC_VSYNC: IC4.11 (PI9); also elsewhere on the board
MCLK_25: IC4.122 (PC9); also elsewhere on the board
unnamed: B1.2 (+), JP2.NC
unnamed: IC4.100 (VCAPDSI), IC4.106 (VDD12DSI)
OE_SYNC: IC4.94 (PD13); also elsewhere on the board
OUT_PAR: IC4.140 (PC11); also elsewhere on the board
OUT_SER: IC4.152 (PG9); also elsewhere on the board
PWR_DIRECT: IC4.110 (PG2); also elsewhere on the board
PWR_SSTART: IC4.111 (PG3); also elsewhere on the board
RCC_OSC_IN: C8.2, IC4.29 (PH0), R14.2, Y1.2
RCC_OSC_OUT: C9.2, IC4.30 (PH1), R14.1, Y1.1
SDMMC1_CK: IC4.141 (PC12); also elsewhere on the board
SDMMC1_CMD: IC4.144 (PD2); also elsewhere on the board
SDMMC1_D0: IC4.121 (PC8); also elsewhere on the board
SD_DETECT: IC4.24 (PF6); also elsewhere on the board
SPI2_CLK: IC4.133 (PI1); also elsewhere on the board
SPI2_CSA: IC4.93 (PD12); also elsewhere on the board
SPI2_CSB: IC4.92 (PD11); also elsewhere on the board
SPI2_IRQ: IC4.123 (PA8); also elsewhere on the board
SPI2_MISO: IC4.87 (PB14); also elsewhere on the board
SPI2_MOSI: IC4.134 (PI3); also elsewhere on the board
SPI4_CLK: IC4.1 (PE2); also elsewhere on the board
SPI4_CSA: IC4.2 (PE3); also elsewhere on the board
SPI4_CSB: IC4.3 (PE4); also elsewhere on the board
SPI4_IRQ: IC4.168 (PB9); also elsewhere on the board
SPI4_MISO: IC4.4 (PE5); also elsewhere on the board
SPI4_MOSI: IC4.5 (PE6); also elsewhere on the board
SPI5_CLK: IC4.25 (PF7); also elsewhere on the board
SPI5_CSA: IC4.157 (PG14); also elsewhere on the board
SPI5_CSB: IC4.156 (PG13); also elsewhere on the board
SPI5_IRQ: IC4.79 (PB10); also elsewhere on the board
SPI5_MISO: IC4.26 (PF8); also elsewhere on the board
SPI5_MOSI: IC4.27 (PF9); also elsewhere on the board
SYS_JTCK-SWCLK: IC4.137 (PA14); also elsewhere on the board
SYS_JTDI: IC4.138 (PA15); also elsewhere on the board
SYS_JTDO-SWO: IC4.161 (PB3); also elsewhere on the board
SYS_JTMS-SWDIO: IC4.128 (PA13); also elsewhere on the board
SYS_JTRST: IC4.162 (PB4); also elsewhere on the board
TFT_BRIGHTNESS: IC4.88 (PB15); also elsewhere on the board
USB_OTG_FS_D_N: IC4.126 (PA11); also elsewhere on the board
USB_OTG_FS_D_P: IC4.127 (PA12); also elsewhere on the board
USB_OTG_FS_ID: IC4.125 (PA10); also elsewhere on the board
USB_OTG_FS_PSO: IC4.147 (PD5); also elsewhere on the board
USB_OTG_FS_VBUS: IC4.124 (PA9); also elsewhere on the board
USER_SW: IC4.163 (PB5); also elsewhere on the board
VBAT: IC4.6 (VBAT), JP2.COM
VCAP1: C34.1, IC4.81 (VCAP_1)
VCAP2: C33.1, IC4.129 (VCAP_2)
VDD: C13.1, C14.1, C15.1, C16.1, C17.1, C18.1, C19.+, C20.1, C21.1, C22.1, C23.1, C24.1, C25.1, C26.1, C27.1, C28.1, C29.1, C30.1, IC4.15 (VDD_2), IC4.23 (VDD_3), IC4.36 (VDD_4), IC4.49 (VDD_5), IC4.62 (VDD_6), IC4.72 (VDD_7), IC4.82 (VDD_8), IC4.96 (VDD_9), IC4.99 (VDDDSI), IC4.118 (VDDUSB), IC4.131 (VDD_10), IC4.136 (VDD_11), IC4.149 (VDDSDMMC), IC4.159 (VDD_12), IC4.171 (PDR_ON), IC4.172 (VDD), JP1.NO, JP2.NO, L1.P$1 (1), R11.1, R17.2
VDDA: C31.1, C32.1, IC4.39 (VDDA), L1.P$2 (2), R18.2
VREF+: IC4.38 (VREF+), R18.1

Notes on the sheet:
Licensed under the TAPR Open Hardware License (www.tapr.org/OHL)
Repository: https://github.com/eez-open
More info at http://www.envox.hr/eez
STM32F7 MCU

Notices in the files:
parts and their libraries:
EEZ_DIB: This work is licensed under the TAPR Open Hardware License.
COPYRIGHT: Copyright C 2016 Accelerated Designs. All rights reserved
